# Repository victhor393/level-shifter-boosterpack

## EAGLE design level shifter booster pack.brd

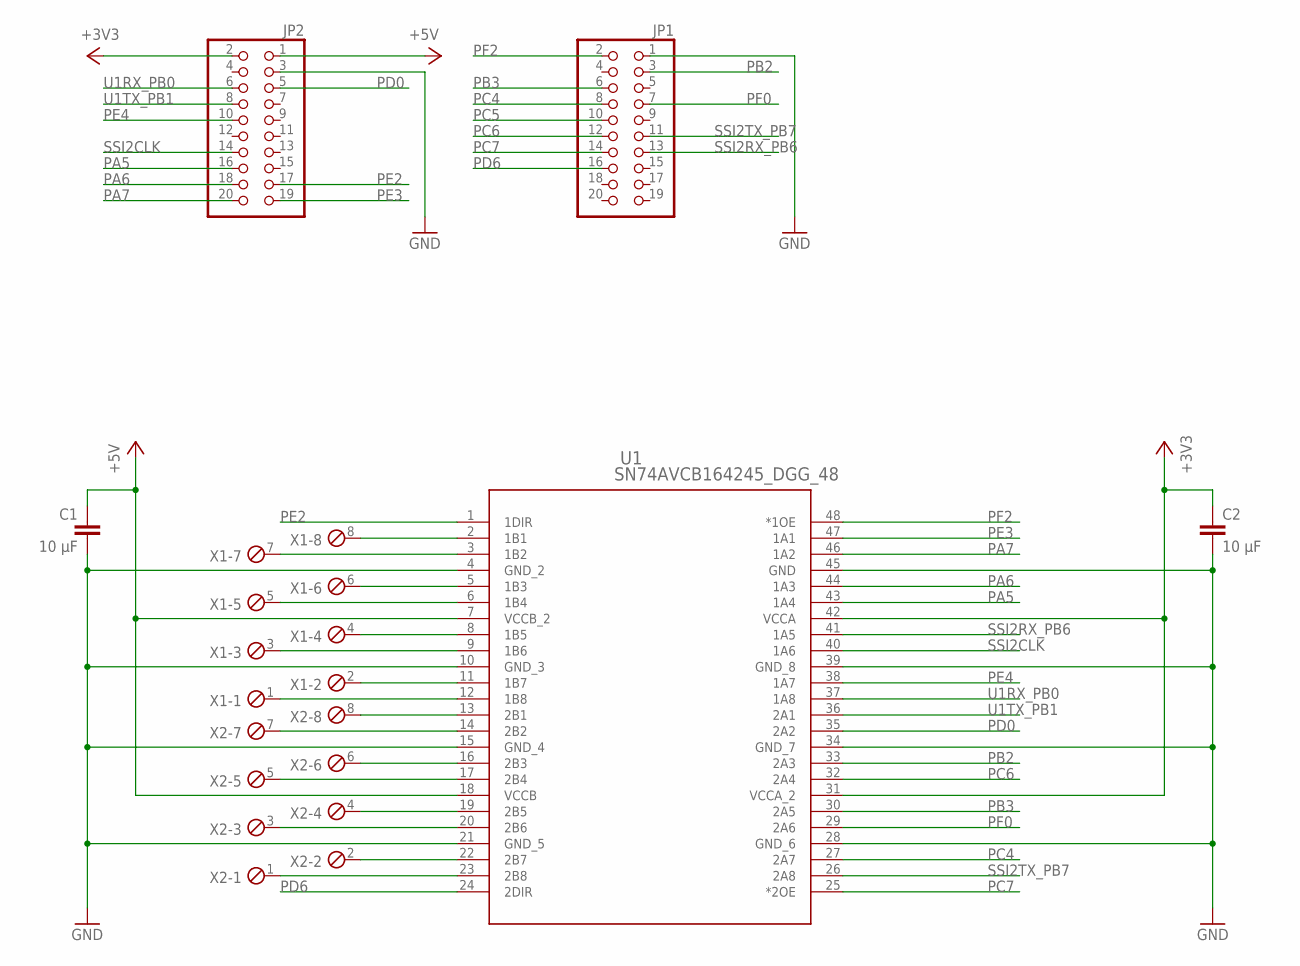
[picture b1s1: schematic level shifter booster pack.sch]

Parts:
C1, C2: 10 µF; C0805
JP1, JP2: PINHD-2X10; 2X10
U1: SN74AVCB164245_DGG_48; DGG48
X1, X2: MPT8; 8POL254

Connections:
+3V3: C2.1, JP2.2, U1.31 (VCCA_2), U1.42 (VCCA)
+5V: C1.1, JP2.1, U1.7 (VCCB_2), U1.18 (VCCB)
GND: C1.2, C2.2, JP1.1, JP2.3, U1.4 (GND_2), U1.10 (GND_3), U1.15 (GND_4), U1.21 (GND_5), U1.28 (GND_6), U1.34 (GND_7), U1.39 (GND_8), U1.45 (GND)
unnamed: U1.2 (1B1), X1.8
unnamed: U1.3 (1B2), X1.7
unnamed: U1.5 (1B3), X1.6
unnamed: U1.6 (1B4), X1.5
unnamed: U1.8 (1B5), X1.4
unnamed: U1.9 (1B6), X1.3
unnamed: U1.11 (1B7), X1.2
unnamed: U1.12 (1B8), X1.1
unnamed: U1.13 (2B1), X2.8
unnamed: U1.14 (2B2), X2.7
unnamed: U1.16 (2B3), X2.6
unnamed: U1.17 (2B4), X2.5
unnamed: U1.19 (2B5), X2.4
unnamed: U1.20 (2B6), X2.3
unnamed: U1.22 (2B7), X2.2
unnamed: U1.23 (2B8), X2.1
PA5: JP2.16, U1.43 (1A4)
PA6: JP2.18, U1.44 (1A3)
PA7: JP2.20, U1.46 (1A2)
PB2: JP1.3, U1.33 (2A3)
PB3: JP1.6, U1.30 (2A5)
PC4: JP1.8, U1.27 (2A7)
PC5: JP1.10
PC6: JP1.12, U1.32 (2A4)
PC7: JP1.14, U1.25 (*2OE)
PD0: JP2.5, U1.35 (2A2)
PD6: JP1.16, U1.24 (2DIR)
PE2: JP2.17, U1.1 (1DIR)
PE3: JP2.19, U1.47 (1A1)
PE4: JP2.10, U1.38 (1A7)
PF0: JP1.7, U1.29 (2A6)
PF2: JP1.2, U1.48 (*1OE)
SSI2CLK: JP2.14, U1.40 (1A6)
SSI2RX_PB6: JP1.13, U1.41 (1A5)
SSI2TX_PB7: JP1.11, U1.26 (2A8)
U1RX_PB0: JP2.6, U1.37 (1A8)
U1TX_PB1: JP2.8, U1.36 (2A1)

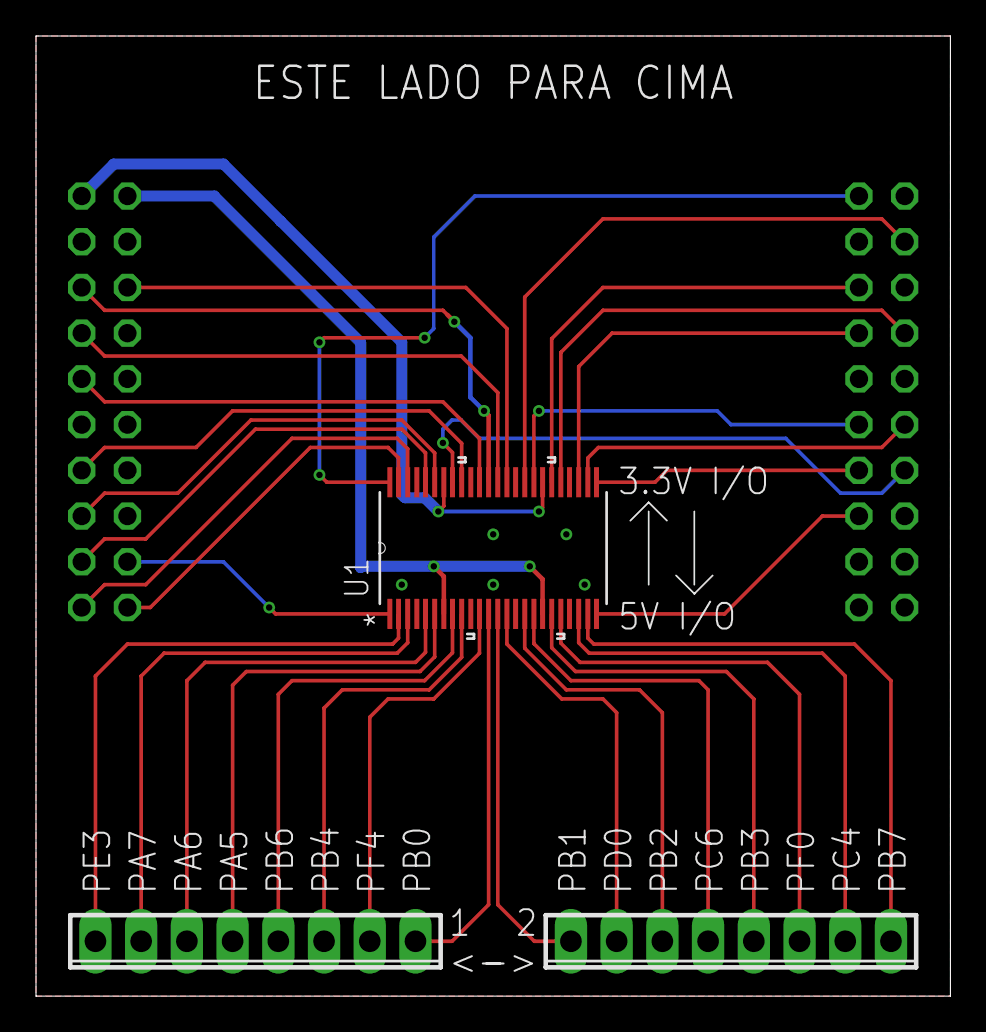
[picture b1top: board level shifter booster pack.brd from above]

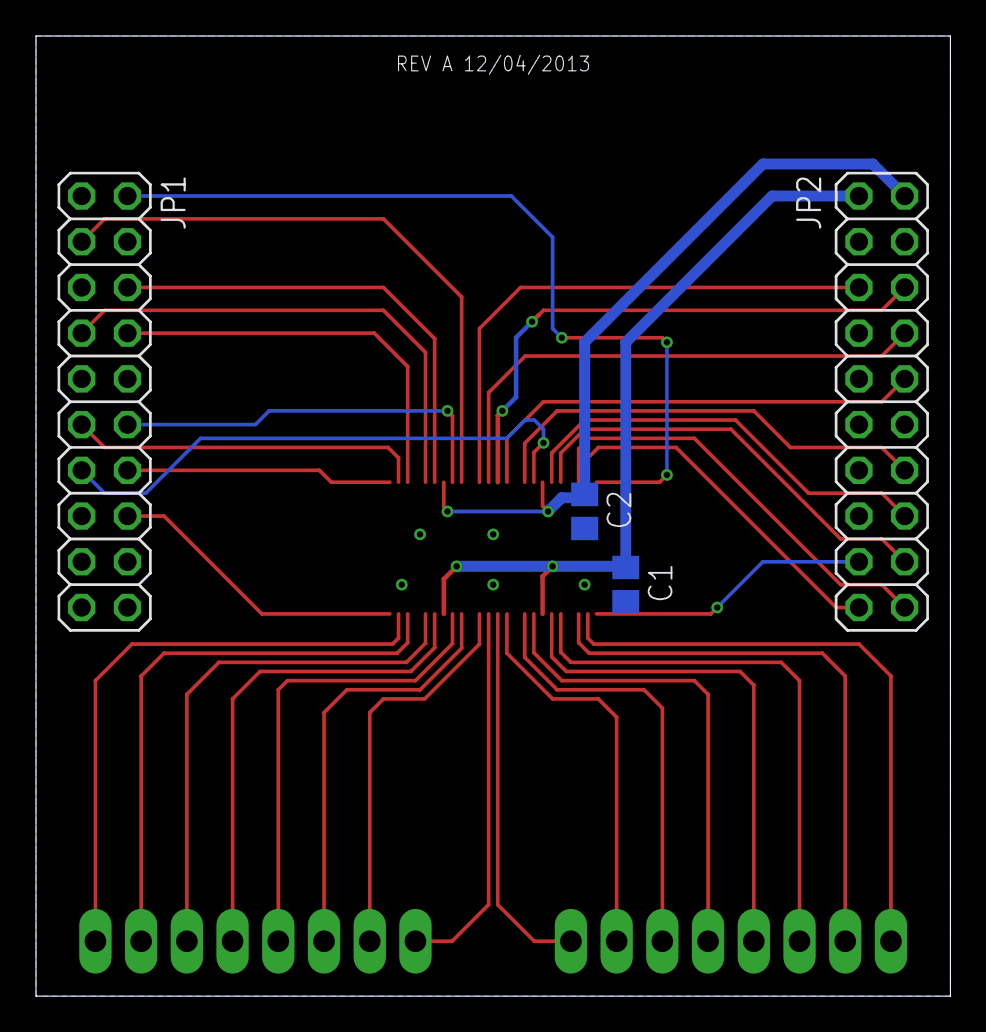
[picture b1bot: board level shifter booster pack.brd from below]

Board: 2 copper layers, 50.8 x 53.3 mm, 7 parts (4 on the bottom side), 39 nets.

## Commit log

2019-05-21 Added schematic and board layout in pdf format
